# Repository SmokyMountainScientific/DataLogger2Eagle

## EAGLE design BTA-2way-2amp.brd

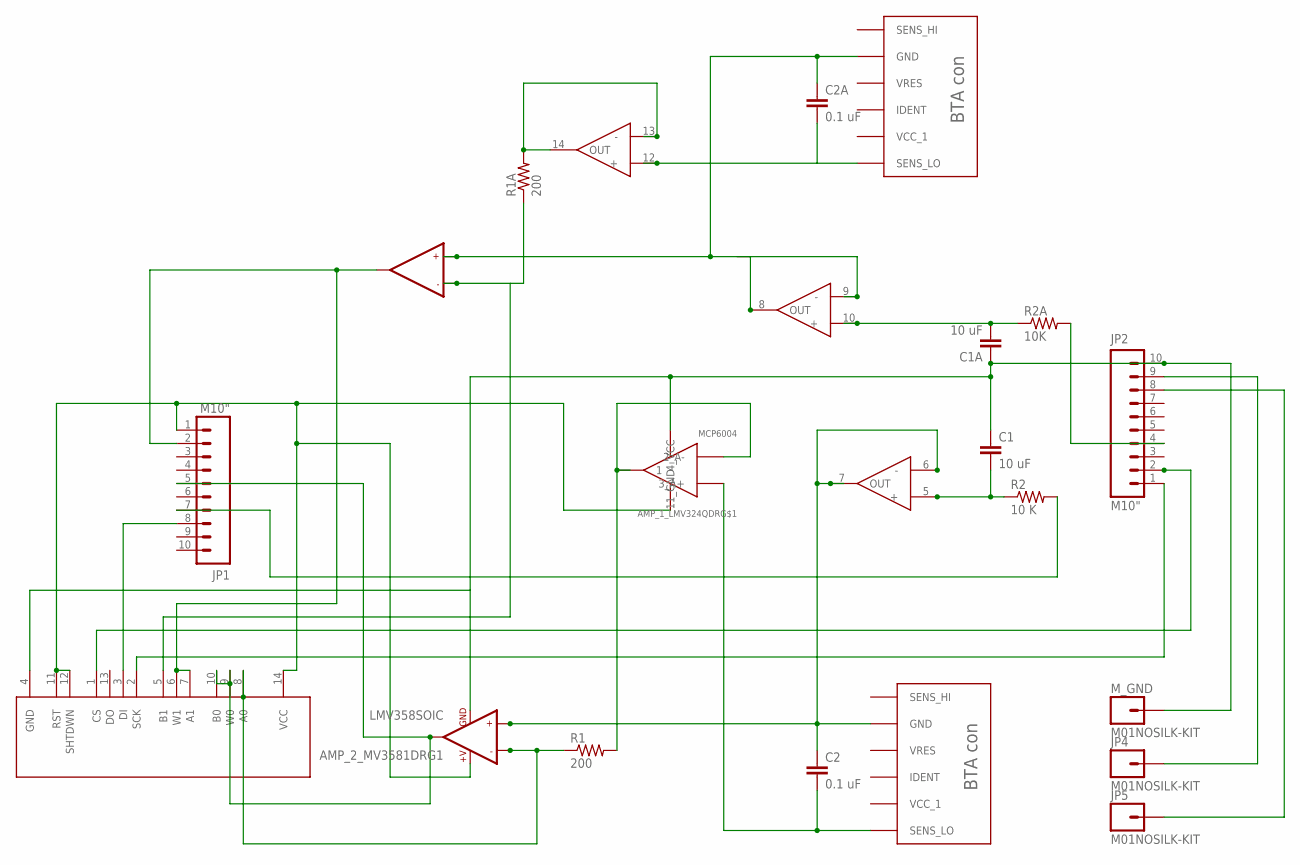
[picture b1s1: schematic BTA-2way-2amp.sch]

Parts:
AMP_1_LMV324QDR: MCP6004; SO014
AMP_2_MV3581DR: LMV358SOIC; SO08
C1, C1A: 10 uF; C1206
C2, C2A: 0.1 uF; C1206
JP1, JP2: M10"; 1X10
JP4, JP5: M01NOSILK-KIT; 1X01NS-KIT
M_GND: M01NOSILK-KIT; 1X01NS-KIT
POT-MCP4231: MCP42XXX; SO014
R1, R1A: 200; R1206
R2: 10 K; R1206
R2A: 10K; R1206
U$1, U$3: BTA_CON

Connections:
unnamed: AMP_1_LMV324QDR.4 (4_VCC), AMP_2_MV3581DR.8 (+V), JP1.1, POT-MCP4231.11 (RST), POT-MCP4231.12 (SHTDWN), POT-MCP4231.14 (VCC)
unnamed: AMP_1_LMV324QDR.11 (11_GND), AMP_2_MV3581DR.4 (GND), C1.1, C1A.1, JP2.10, M_GND.1, POT-MCP4231.4 (GND)
unnamed: AMP_1_LMV324QDR.3 (3_A+), C2.2, U$3.PIN_6 (SENS_LO)
unnamed: AMP_2_MV3581DR.2 (-IN1), POT-MCP4231.8 (A0), R1.1
unnamed: JP1.8, POT-MCP4231.3 (DI)
unnamed: AMP_2_MV3581DR.1 (OUT1), JP1.5, POT-MCP4231.9 (W0), POT-MCP4231.10 (B0)
unnamed: JP1.7, R2.2
unnamed: AMP_1_LMV324QDR.1, AMP_1_LMV324QDR.2 (2_A-), R1.2
unnamed: AMP_1_LMV324QDR.5 (+), C1.2, R2.1
unnamed: JP2.2, POT-MCP4231.1 (CS)
unnamed: JP2.1, POT-MCP4231.2 (SCK)
unnamed: AMP_1_LMV324QDR.6 (-), AMP_1_LMV324QDR.7 (OUT), AMP_2_MV3581DR.3 (+IN1), C2.1, U$3.PIN_2 (GND)
unnamed: JP2.4, R2A.2
unnamed: AMP_1_LMV324QDR.10 (+), C1A.2, R2A.1
unnamed: AMP_1_LMV324QDR.8 (OUT), AMP_2_MV3581DR.5 (+IN2), C2A.1, U$1.PIN_2 (GND)
unnamed: AMP_1_LMV324QDR.12 (+), C2A.2, U$1.PIN_6 (SENS_LO)
unnamed: AMP_2_MV3581DR.7 (OUT2), JP1.2, POT-MCP4231.6 (W1), POT-MCP4231.7 (A1)
unnamed: AMP_2_MV3581DR.6 (-IN2), POT-MCP4231.5 (B1), R1A.1
unnamed: JP2.9, JP4.1
unnamed: AMP_1_LMV324QDR.13 (-), AMP_1_LMV324QDR.14 (OUT), R1A.2
unnamed: JP2.8, JP5.1

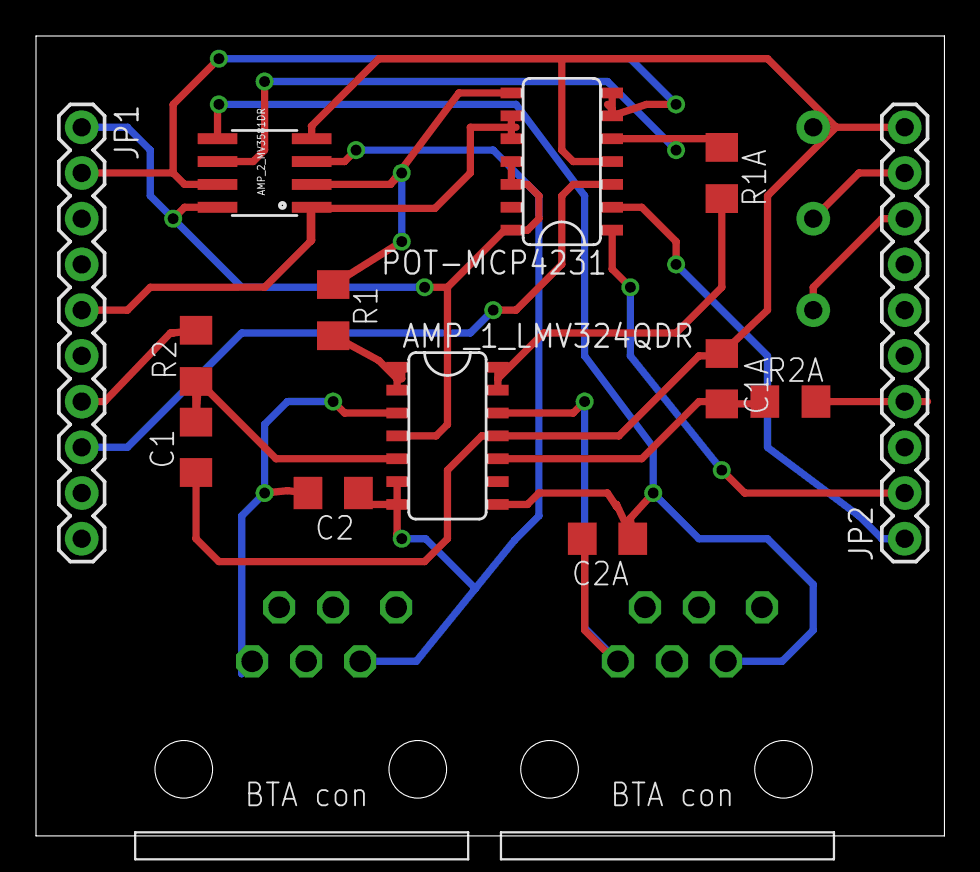
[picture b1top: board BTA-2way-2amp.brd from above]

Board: 2 copper layers, 50.5 x 44.4 mm, 18 parts (0 on the bottom side), 21 nets.

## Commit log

2014-11-24 :lollipop: Added .gitattributes & .gitignore files
2014-11-24 Eagle brd and sch files for Datalogger2
    Datalogger2 is a boosterpack (or shield) for the Texas Instruments Tiva
    C LaunchPad. That allows amplification of voltages between 0 and 3.3
    volts

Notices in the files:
parts and their libraries:
SparkFun-Connectors: Licensing: Creative Commons ShareAlike 4.0 International - https://creativecommons.org/licenses/by-sa/4.0
